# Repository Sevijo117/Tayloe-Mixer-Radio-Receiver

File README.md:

"# Tayloe-Mixer-Radio Receiver" 
# Tayloe-Mixer-Radio-Receiver

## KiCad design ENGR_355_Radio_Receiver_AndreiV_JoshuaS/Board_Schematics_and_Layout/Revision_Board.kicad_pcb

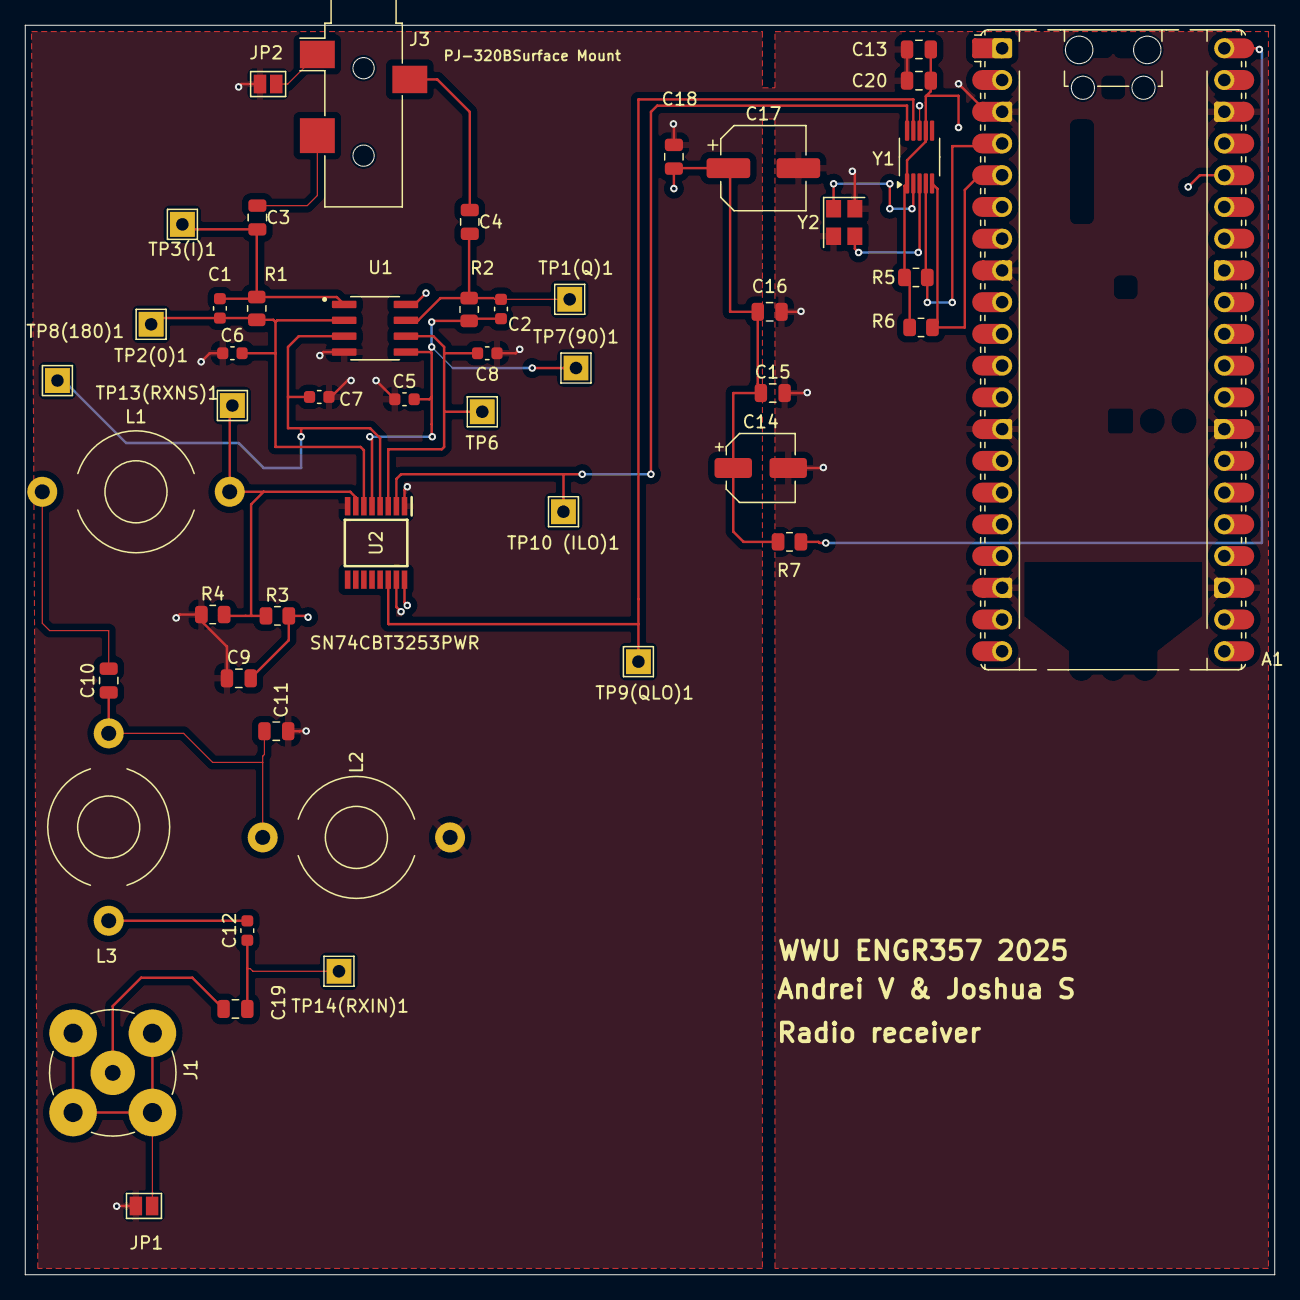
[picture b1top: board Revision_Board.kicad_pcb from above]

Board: 4 copper layers, 100.0 x 100.0 mm, 49 parts (0 on the bottom side), 26 nets.

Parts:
A1: RaspberryPi_Pico; RaspberryPi_Pico_Common_Unspecified
C1, C2, C5, C6, C7, C8: 6.8nF; C_0603_1608Metric
C3, C4: 1uF; C_0805_2012Metric
C9, C16, C18, C19, C20: 100nF; C_0805_2012Metric
C10: 510pF; C_0805_2012Metric
C11: 360pF; C_0805_2012Metric
C12: 1.6nF; C_0603_1608Metric
C13: 22pF; C_0805_2012Metric
C14: 100uF; CP_Elec_5x5.4
C15: 10uF; C_0805_2012Metric
C17: 220uF; CP_Elec_6.3x5.4
J1: Conn_Coaxial; BNC_TEConnectivity_1478204_Vertical
J3: PJ-320BSurface Mount; Jack_3.5mm_CUI_SJ-3523-SMT_Horizontal
JP1, JP2: Jumper_2_Open; SolderJumper-2_P1.3mm_Open_Pad1.0x1.5mm
L1: 1uH; L_Toroid_Horizontal_D9.5mm_P15.00mm_Diameter10-5mm_Amidon-T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
L2: 1.5uH; L_Toroid_Horizontal_D9.5mm_P15.00mm_Diameter10-5mm_Amidon-T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
L3: 330nH; L_Toroid_Horizontal_D9.5mm_P15.00mm_Diameter10-5mm_Amidon-T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
R1, R2: 250; R_0805_2012Metric
R3, R4: 10k; R_0805_2012Metric
R5, R6: 4.7k; R_0805_2012Metric
R7: 10; R_0805_2012Metric
TP1(Q)1, TP2(0)1, TP3(I)1, TP6, TP7(90)1, TP8(180)1, TP9(QLO)1, TP10 (ILO)1, TP13(RXNS)1, TP14(RXIN)1: TestPoint; TestPoint_THTPad_2.0x2.0mm_Drill1.0mm
U1: TLV2172IDR; SOIC127P599X175-8N
U2: SN74CBT3253PWR; SOP65P640X120-16N
Y1: MS5351M; MSOP-10_3x3mm_P0.5mm
Y2: XC322525MOB4SA-18; Crystal_SMD_TXC_7M-4Pin_3.2x2.5mm

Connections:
+3.3V: A1.36 (3V3), C13.1, C20.1, R5.2, R6.2, Y1.1 (VDD), Y1.7 (VDDO)
+5V: A1.40 (VBUS), R7.1
GND: A1.3 (GND), A1.8 (GND), A1.13 (GND), A1.18 (GND), A1.23 (GND), A1.28 (GND), A1.38 (GND), C5.1, C6.1, C7.1, C8.1, C9.1, C11.2, C13.2, C14.2, C15.2, C16.2, C17.2, C18.2, C20.2, JP1.2 (B), JP2.1 (A), L2.2, R4.1, U1.4 (VCC-), U2.1 (1~OE), U2.8 (GND), U2.15 (2~OE), Y1.8 (GND), Y2.2, Y2.4
GPIO2: A1.4 (GPIO2), R5.1, Y1.4 (SCL)
GPIO3: A1.5 (GPIO3), R6.1, Y1.5 (SDA)
I: C3.1, J3.T
unnamed: C10.1, C11.1, L2.1, L3.2
unnamed: C10.2, L1.1
unnamed: C12.1, C19.2, TP14(RXIN)1.1
unnamed: C12.2, L3.1
unnamed: J1.2 (Ext), JP1.1 (A)
unnamed: C19.1, J1.1 (In)
unnamed: J3.S, JP2.2 (B)
unnamed: C7.2, TP8(180)1.1, U1.3 (1IN+), U2.4 (1B3)
unnamed: C1.2, C6.2, R1.2, TP2(0)1.1, U1.2 (1IN-), U2.6 (1B1)
unnamed: C1.1, C3.2, R1.1, TP3(I)1.1, U1.1 (1OUT)
unnamed: C8.2, TP6.1, U1.6 (2IN+), U2.3 (1B4)
unnamed: C2.2, C5.2, R2.2, TP7(90)1.1, U1.5 (2IN-), U2.5 (1B2)
unnamed: C2.1, C4.2, R2.1, TP1(Q)1.1, U1.7 (2OUT)
unnamed: L1.2, R3.1, R4.2, TP13(RXNS)1.1, U2.7 (1A)
unnamed: TP9(QLO)1.1, U2.14 (S0), Y1.9 (CLK1)
unnamed: TP10 (ILO)1.1, U2.2 (S1), Y1.10 (CLK0)
unnamed: Y1.2 (XA), Y2.1
unnamed: Y1.3 (XB), Y2.3
Q: C4.1, J3.R
Smoothed 5V: C9.2, C14.1, C15.1, C16.1, C17.1, C18.1, R3.2, R7.2, U1.8 (VCC+), U2.16 (VCC)

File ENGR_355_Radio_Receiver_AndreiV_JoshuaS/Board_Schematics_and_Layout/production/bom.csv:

Designator,Footprint,Quantity,Value,LCSC Part #
A1,RaspberryPi_Pico_Common_Unspecified,1,RaspberryPi_Pico,
"C1, C2, C5, C6, C7, C8",0603,6,6.8nF,
C10,0805,1,510pF,
C11,0805,1,360pF,
C12,0603,1,1.6nF,
C13,0805,1,22pF,
C14,CP_Elec_5x5.4,1,100uF,
C15,0805,1,10uF,
"C16, C18, C19, C20, C9",0805,5,100nF,
C17,CP_Elec_6.3x5.4,1,220uF,
"C3, C4",0805,2,1uF,
J1,BNC_TEConnectivity_1478204_Vertical,1,Conn_Coaxial,
J3,Jack_3.5mm_CUI_SJ-3523-SMT_Horizontal,1,PJ-320BSurface Mount,
"JP1, JP2",SolderJumper-2_P1.3mm_Open_Pad1.0x1.5mm,2,Jumper_2_Open,
"R1, R2",0805,2,250,
"R3, R4",0805,2,10k,
"R5, R6",0805,2,4.7k,
R7,0805,1,10,
"TP1(Q)1, TP10 (ILO)1, TP13(RXNS)1, TP14(RXIN)1, TP2(0)1, TP3(I)1, TP6, TP7(90)1, TP8(180)1, TP9(QLO)1",TestPoint_THTPad_2.0x2.0mm_Drill1.0mm,10,TestPoint,
U1,SOIC127P599X175-8N,1,TLV2172IDR,
U2,SOP65P640X120-16N,1,SN74CBT3253PWR,
Y1,MSOP-10_3x3mm_P0.5mm,1,MS5351M,
Y2,Crystal_SMD_TXC_7M-4Pin_3.2x2.5mm,1,XC322525MOB4SA-18,

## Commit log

2025-06-12 clean upload of project
